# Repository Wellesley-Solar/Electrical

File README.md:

# Electrical
Electrical work for the lab

## Lighting
A board with a 450nm LED for testing perovskite samples. More details [here](https://github.com/Wellesley-Solar/Electrical/blob/master/Lighting/README.md).

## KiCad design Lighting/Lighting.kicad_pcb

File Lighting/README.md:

# Lighting Board

Updated: August 4th, 2020

The lighting board is equipped with a 450nm, blue LED with manually or digitally tunable radiative power. The USB-SPI bridge available allows users to send digital commands on a laptop to the digital analog converter (DAC) to effectively control the current through the 450nm LED. When connected with the thumbwheel potentiometer, the current through the 450nm LED can be similarly tuned to a upward limit of 1A.

## Power Supply
The 450nm LED, which draws a maximum of 3A, can be powered through a USB-C connection. A USB-C wall adapter with 5.1V/30.A DC output would suffice. An example would be a [Raspberry Pi 15.3W USB-C Power Supply](https://www.raspberrypi.org/products/type-c-power-supply/). Alternatively, the LED can be powered through a desktop power supply by connecting the pin labelled `ext LED pwr` on JP5 and grounding the power supply and PCB together. For more, see the PCB silkscreen.

The on-board electronics are powered through the USB micro. For manual control, it is sufficient to connect it directly to a wall adapter or a battery bank. For more precise digital control, it is necessary to connect the USB micro to a laptop, because the DAC would reset to 0V after a power cycle. To power the electronics with a desktop power supply, connect 5V to `TP3/Vcc` on the PCB and ground the power supply with the PCB.

## Control
### Manual
To control the amount of lighting through the thumbwheel `RV1`, connect the two pins labeled `POT` on the jumper `JP3`. The range of current output is approximately 0-1A.
#### Waveform Generator
To use a waveform generator on the LED, keep `JP3` in the `POT` connection. Ground the PCB and the waveform generator together, and connect the waveform generator output to the pin labeled `wave gen->` on `JP2`. The current through LED can be adjusted through the waveform generator or through the thumbwheel.

### Digital
Connect the USB micro on the PCB to a computer. MCP2210 Utility is a convenient GUI to communicate over SPI with DAC.
More details after being implemented and tested once the physical board is assembled and functional.

## Sample Mounting
The 450nm LED sits in the middle of a 20mm*20mm sqaure. Three corners of the square are drilled with holes of 4.5mm diameter. A 3D printed stand can be designed to fit into the holes. The samples to be tested can then be mounted on top of the stand with an appropriate opening.  

## LED Intensity
`/Calculations` contains the specification data for the 450nm LED and a Matlab file for calculating the relevant radiative intensity.
The Matlab file follows through examples of such calculations. To begin with, let us suppose that the solar intensity is `1000W/m^2`, the number of photons with <500nm wavelength in solar radiation `numPhoton` is roughly `4.16*10^20`, and the sample size, `deviceArea`, is `20mm*20mm=4*10^-4m^2`. From the datasheet for the 450nm LED, we know that the PPF efficacy is `2.73(uMol/s)/W`. Converting PPF efficacy to photon number efficacy, we multiply the PPF efficacy by `1e-6*6.022*1e23`. Assuming all radiative power is absorbed by the perovskite sample, that is `percentAbsorbed`, the amount of electrical power needed for the LED is given by:
```
electricalNeed = numPhoton*deviceArea./(photonNumEfficacy*percentAbsorbed)
```
Given the electrical power in demand, we open the `Electrical Power vs. Forward Current` plot and find a corresponding electrical power. To adjust for the fact that not all photons are absorbed by perovskite samples, open the `Cumulative Percent Radiant Power within an Angle` plot, which gives the percentage of all photons falling within a given central amount of angle in degrees. For instance, if the perovskite sample covers the central 53 degrees directly above the 450nm LED, the amount of photon within this angle is matched to 43.78%.

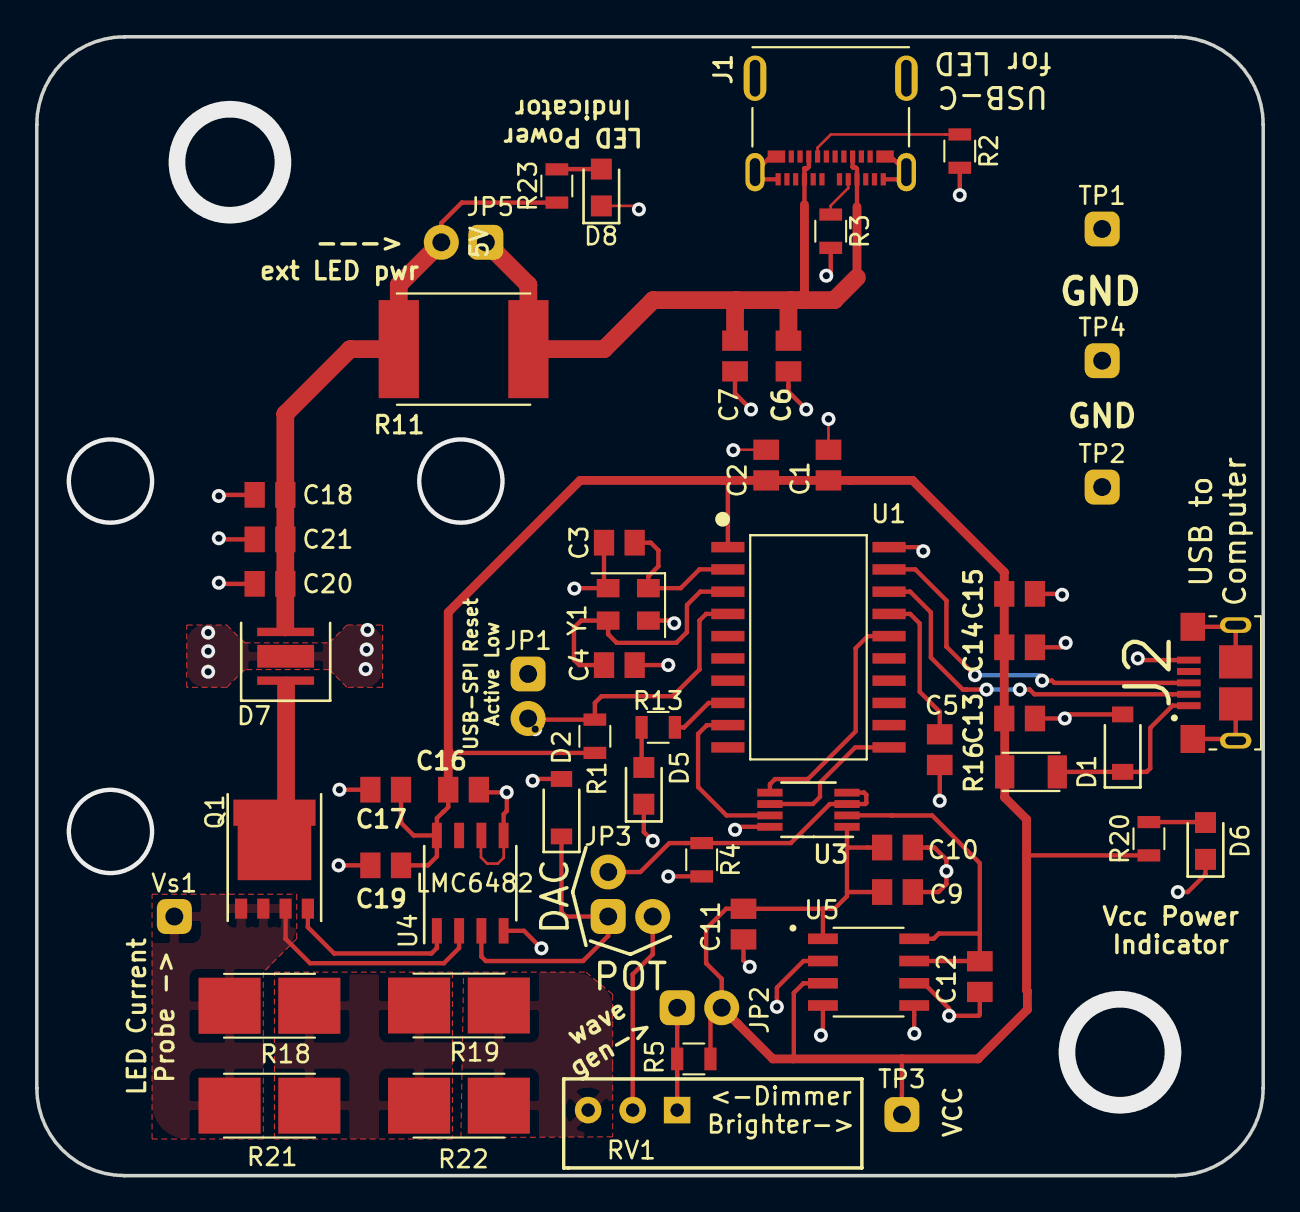
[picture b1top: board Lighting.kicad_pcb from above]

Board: 2 copper layers, 70.0 x 65.0 mm, 58 parts (0 on the bottom side), 29 nets.

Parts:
C1, C9, C14, C17, C18: C_0u1; C_0805
C2, C6, C10, C15, C19, C20: C_1u; C_0805
C3, C4: C_12p; C_0805
C5, C11: C_0u47; C_0805
C7, C13, C21: C_10u; C_0805
C12, C16: C_1n; C_0805
D1, D2: D_Zener_5v6; SOD123
D5, D6, D8: LED_645nm; LED0805
D7: LED_PAD_450nm; SST-20-A120
J1: USB_C_Receptacle; MOLEX_105450-0101
J2: USB_B_Micro; FCI_10118193-0001LF
JP1, JP2, JP5: Jumper_NO_Small; jumper_2
JP3: Jumper_3; jumper_3
Q1: PSMN011; Power_SO8
R1, R13, R20, R23: R_1k; R0805
R2, R3: R_5k1; R0805
R4: R_10k; R0805
R5: R_39k2; R0805
R11: PTC_1A5; RESC2920
R16: PTC_1A; RESC3216X125N
R18, R19, R21, R22: R_1_2512; R_2512_2W
RV1: R_TW_10k; POT_3352W
TP1, TP2, TP3, TP4: TestPoint; TP
U1: MCP2210T-I_SO; SOIC127P1030X265-20N
U3: DAC6551AQDGKRQ1; SOP65P490X110-9N
U4: LMC6482; LMC6482AIMX&slash_NOPB
U5: MCP1501_2v5; SOIC127P600X175-8N
Vs1: TestPoint; TP
Y1: Crystal_12MHz; Kyocera_Crystal

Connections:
+5V: C18.1, C20.1, C21.1, D7.2, JP5.2, R11.1, R23.1
/CS_DAC: U1.16, U3.5
/D+: J2.3, U1.19
/D-: J2.2, U1.18
/MOSI: U1.9, U3.7
/SCK: U1.11, U3.6
GND: C1.2, C2.2, C3.2, C4.2, C5.2, C6.2, C7.2, C9.2, C10.2, C11.2, C12.2, C13.2, C14.2, C15.2, C16.2, C17.2, C18.2, C19.2, C20.2, C21.2, D1.2, D2.2, D5.1, D6.1, D7.3, D8.1, J1.A1, J1.A12, J1.B1, J1.B12, J1.S1, J2.5, J2.6, JP1.1, R2.2, R3.2, R4.2, R19.2, R22.2, RV1.3, TP1.1, TP2.1, TP4.1, U1.20, U3.8, U4.4, U4.5, U4.6, U5.2, U5.4, U5.5, U5.6, Y1.2, Y1.4
unnamed: C3.1, U1.2, Y1.1
unnamed: C4.1, U1.3, Y1.3
unnamed: C5.1, U1.17
unnamed: C6.1, C7.1, J1.A4, J1.A9, J1.B4, J1.B9, JP5.1, R11.2
unnamed: C12.1, U3.2, U5.7, U5.8
unnamed: D1.1, J2.1, R16.2
unnamed: D2.1, JP3.1, U4.3
unnamed: D5.2, R13.2
unnamed: D6.2, R20.2
unnamed: D7.1, Q1.1
unnamed: D8.2, R23.2
unnamed: J1.A5, R3.1
unnamed: J1.B5, R2.1
unnamed: JP1.2, R1.2, U1.4
unnamed: JP2.1, R5.2, RV1.1
unnamed: JP3.2, R4.1, U3.3, U3.4
unnamed: JP3.3, RV1.2
unnamed: Q1.2, U4.1
unnamed: Q1.3, R18.1, R21.1, U4.2, Vs1.1
unnamed: R13.1, U1.8
unnamed: R18.2, R19.1, R21.2, R22.1
VCC: C1.1, C2.1, C9.1, C10.1, C11.1, C13.1, C14.1, C15.1, C16.1, C17.1, C19.1, JP2.2, R1.1, R5.1, R16.1, R20.1, TP3.1, U1.1, U3.1, U4.8, U5.1, U5.3

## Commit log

2020-03-26 initial starting work for light source
2020-04-02 add matlab calculations; add ADC, USB-C, FTIR componenets
2020-04-08 finished schematic for all but USB-C for portable power
2020-04-10 finished schematic with PDF
2020-04-13 add external voltage reference
2020-04-13 correct pot footprint
2020-04-23 finish PCB layout and output gerber
2020-04-23 add latest bom
2020-04-23 try to make it look okay
2020-04-23 look nice
2020-04-23 update gerber
2020-04-23 gerber zip looks good to me
2020-05-12 changes based on feedback
2020-05-12 fix netlist
2020-05-12 latest gerber
2020-08-04 minor trace fix; add readme
2020-08-04 update the main README
2020-08-04 add csv file for calculations
2020-08-23 fix 1u cap link mistake; give mcp2210 correct name
2020-08-23 update schematic pdf
2020-08-23 fix 39k2 resistor error
2021-05-18 lighting protoboard
